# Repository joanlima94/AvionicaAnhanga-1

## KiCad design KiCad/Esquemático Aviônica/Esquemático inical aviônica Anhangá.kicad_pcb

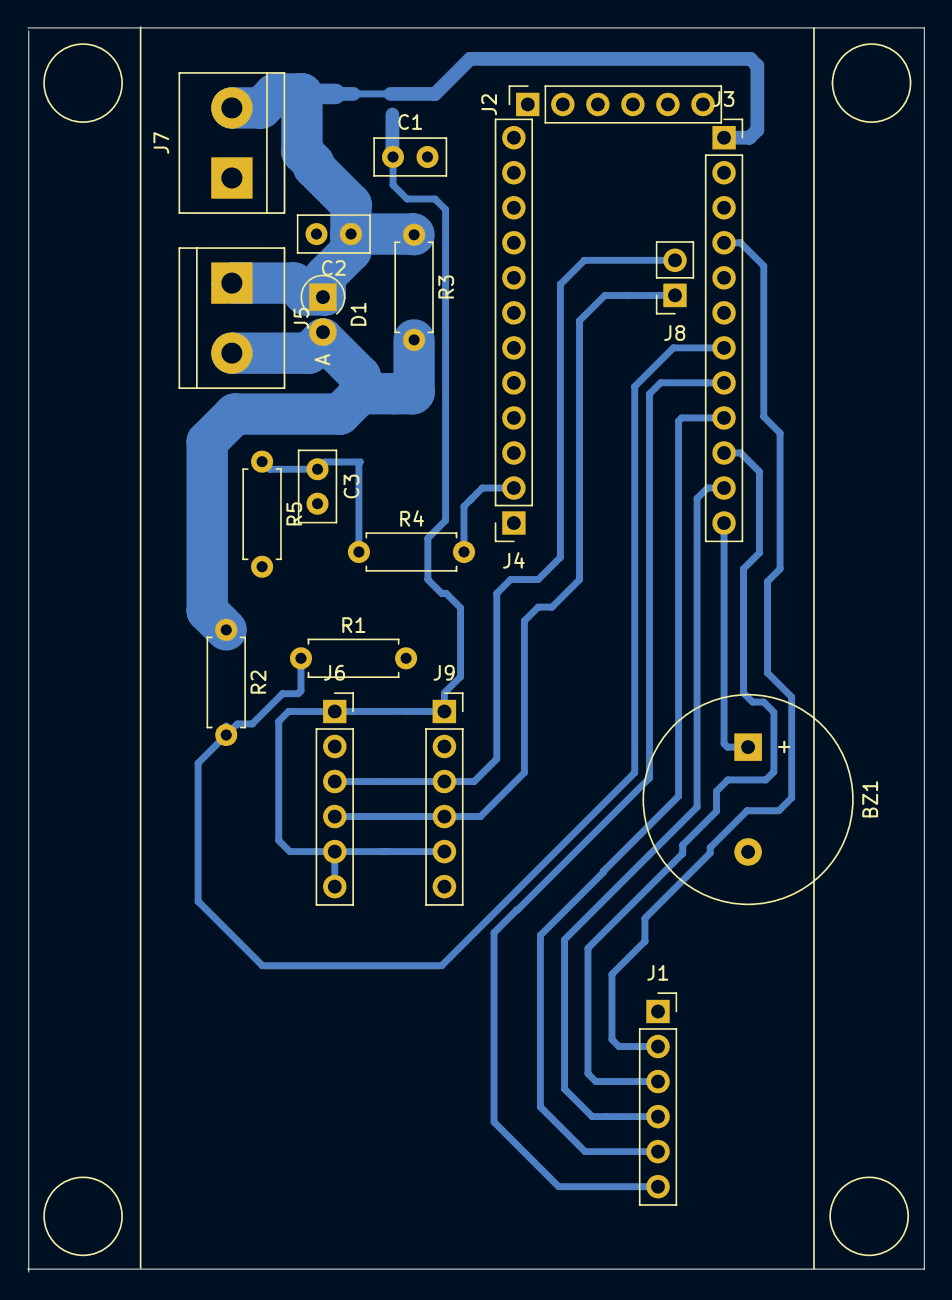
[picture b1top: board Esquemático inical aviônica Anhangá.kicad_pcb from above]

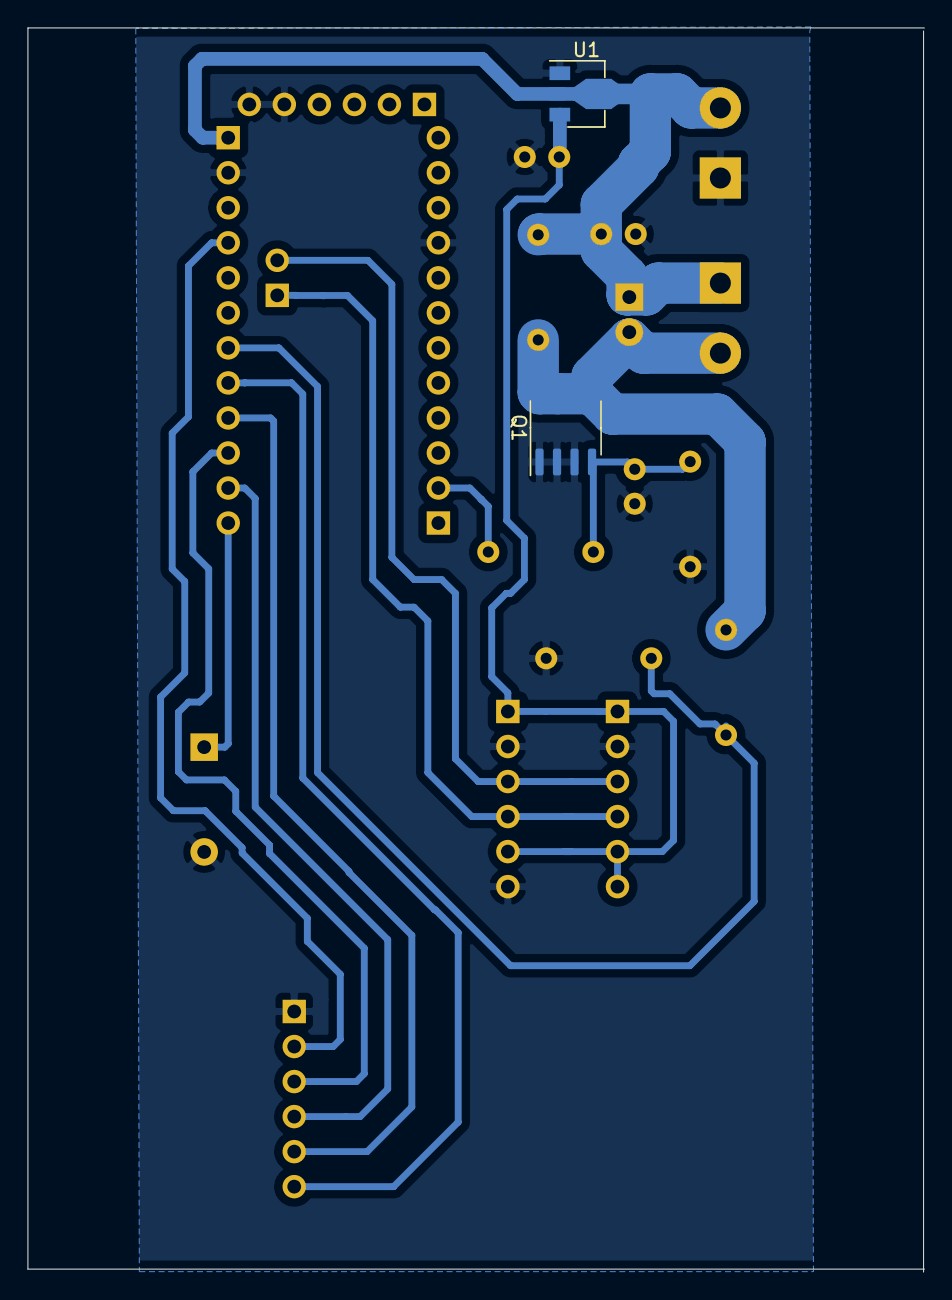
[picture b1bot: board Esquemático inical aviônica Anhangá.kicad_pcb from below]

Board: 2 copper layers, 65.0 x 90.2 mm, 21 parts (2 on the bottom side), 16 nets.

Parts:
BZ1: Buzzer; Buzzer_15x7.5RM7.6
C1, C2: C; C_Disc_D5.0mm_W2.5mm_P2.50mm
C3: 100n; C_Disc_D5.0mm_W2.5mm_P2.50mm
D1: D; D_T-1_P2.54mm_Vertical_AnodeUp
J1, J2: Conn_01x06_Female; PinSocket_1x06_P2.54mm_Vertical
J3, J4: Conn_01x12_Female; PinSocket_1x12_P2.54mm_Vertical
J5, J7: Screw_Terminal_01x02; TerminalBlock_bornier-2_P5.08mm
J6, J9: Conn_01x06_Male; PinSocket_1x06_P2.54mm_Vertical
J8: Conn_01x02_Female; PinSocket_1x02_P2.54mm_Vertical
Q1: IRF7403; SOIC-8_3.9x4.9mm_P1.27mm
R1, R2, R3: R; R_Axial_DIN0207_L6.3mm_D2.5mm_P7.62mm_Horizontal
R4: 1k; R_Axial_DIN0207_L6.3mm_D2.5mm_P7.62mm_Horizontal
R5: 100k; R_Axial_DIN0207_L6.3mm_D2.5mm_P7.62mm_Horizontal
U1: ME620933; SOT-89-3

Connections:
5V: J1.2, J2.4, J3.4
10: BZ1.1, J3.12
ANAL_INPUT_V_NÍQUEL: J3.7, R1.1, R2.2
CS: J1.6, J3.8
D8: J4.2, R4.2
GND: BZ1.2, C1.2, C2.2, C3.2, J1.1, J2.5, J2.6, J3.2, J4.9, J6.2, J7.1, J9.2, J9.6, Q1.1, Q1.2, Q1.3, R1.2, R5.2, U1.1
MISO: J1.3, J3.10
MOSI: J1.4, J3.11
unnamed: C3.1, Q1.4, R4.1, R5.1
unnamed: D1.2, J5.2, Q1.5, Q1.6, Q1.7, Q1.8, R2.1, R3.2
RST: J3.3, J4.10
SCK: J1.5, J3.9
SCL: J6.3, J8.2, J9.3
SDA: J6.4, J8.1, J9.4
VBAT: C2.1, D1.1, J3.1, J5.1, J7.2, R3.1, U1.2
VCC: C1.1, J6.1, J6.5, J6.6, J9.1, J9.5, U1.3

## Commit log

2019-10-12 KiCad
2019-10-12 Esquemático e Layout reformulados
2019-10-12 Atualização do Layout
2019-10-13 Furos posicionados
2019-10-18 Revisão pós montagem
2019-10-18 Atualização pós revisão
2019-10-22 Adicionando novo BMP280
2019-10-23 Atualização Layout
2019-10-23 Atual. Layout + Esquemát.
2019-11-07 Mudança de pinos
2019-12-01 PCB Anhangá
2020-02-16 Esquemático Novo
